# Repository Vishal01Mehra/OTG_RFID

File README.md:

# STM32G0 + MFRC522 RFID Reader

#### This repository provides code and hardware documentation for interfacing the **MFRC522 RFID reader** with an **STM32G0 series microcontroller** over SPI. The firmware initializes the MFRC522, detects RFID cards, and prints their UID over UART. It also includes support for an **addressable RGB LED** (e.g., WS2812B) and a **buzzer** for feedback.

##  Features
- Uses STM32Cube HAL for SPI, GPIO, and TIM
- Reads MIFARE cards (UID output)
- Controls an addressable RGB LED (PA3)
- Activates buzzer on card detection (PA2)
- Compatible with MFRC522 13.56 MHz modules
- Designed for STM32G0xx (e.g., STM32G071, STM32G031)
- Antenna is tuned for best theoretical range (10–15 cm)

>  **Note:** Higher read ranges (>15 cm) are only possible with UHF RFID chipsets (e.g., EPC Gen2, ISO18000-6C), which are significantly more expensive. This project limits itself to a 13.56 MHz MFRC522-based design due to a target **cost constraint of ₹500**, making UHF solutions out of scope.

---

##  Repository Structure
```
├── Core
│   ├── Inc
│   │   └── mfrc522.h           # MFRC522 header file
│   └── Src
│       └── mfrc522.c           # MFRC522 implementation
├── Drivers
│   └── STM32G0xx_HAL_Driver    # HAL drivers
├── README.md                   # This file
├── main.c                      # Main application logic
├── LICENSE                     # GNU GPL v3 license
└── .ioc                        # STM32CubeMX project file
```

---

##  Hardware Connections
### SPI Interface
| MFRC522 Pin | STM32G0 Pin | Description |
|-------------|-------------|-------------|
| SDA (SS)    | PA4         | SPI Chip Select |
| SCK         | PA5         | SPI Clock |
| MOSI        | PA7         | SPI MOSI |
| MISO        | PA6         | SPI MISO |
| RST         | PB0         | Reset Pin |
| 3.3V        | 3.3V        | Power |
| GND         | GND         | Ground |

### Other IOs
| Component         | STM32G0 Pin | Notes                       |
|-------------------|-------------|-----------------------------|
| Buzzer            | PA2         | On for tag detected         |
| RGB LED (WS2812B) | PA3         | 1-wire protocol             |

---

##  Example Output (USB)
```
MFRC522 Reader Initialized
Scan RFID...
UID: DE AD BE EF
```

---

##  Getting Started

### Prerequisites
- STM32CubeIDE or STM32CubeMX
- ST-LINK or compatible debugger
- MFRC522 RFID Module
- WS2812B LED
- Buzzer (active or transistor-driven passive)

### Build & Flash
1. Clone this repo: `https://github.com/Vishal01Mehra/OTG_RFID`
2. Open the `.ioc` file in STM32CubeIDE
3. Generate code and build
4. Flash to STM32G0 MCU

### Dependencies
- STM32 HAL Drivers (auto-imported with `.ioc`)

> 🔧 **Note:** Software is coming soon. Code files will be released as part of the first firmware version.

---

##  References
- [MFRC522 Datasheet](https://www.nxp.com/docs/en/data-sheet/MFRC522.pdf)
- [STM32G0 Reference Manual](https://www.st.com/resource/en/reference_manual/dm00371828.pdf)
- [WS2812B Timing](https://cdn-shop.adafruit.com/datasheets/WS2812B.pdf)

---

##  License
This project is licensed under the **GNU General Public License v3.0** - see the [LICENSE](LICENSE) file for details.

---

## Author
**Vishal Mehra** - Mehra Autonomous Systems Pvt. Ltd.

---

Feel free to contribute or raise issues via GitHub.

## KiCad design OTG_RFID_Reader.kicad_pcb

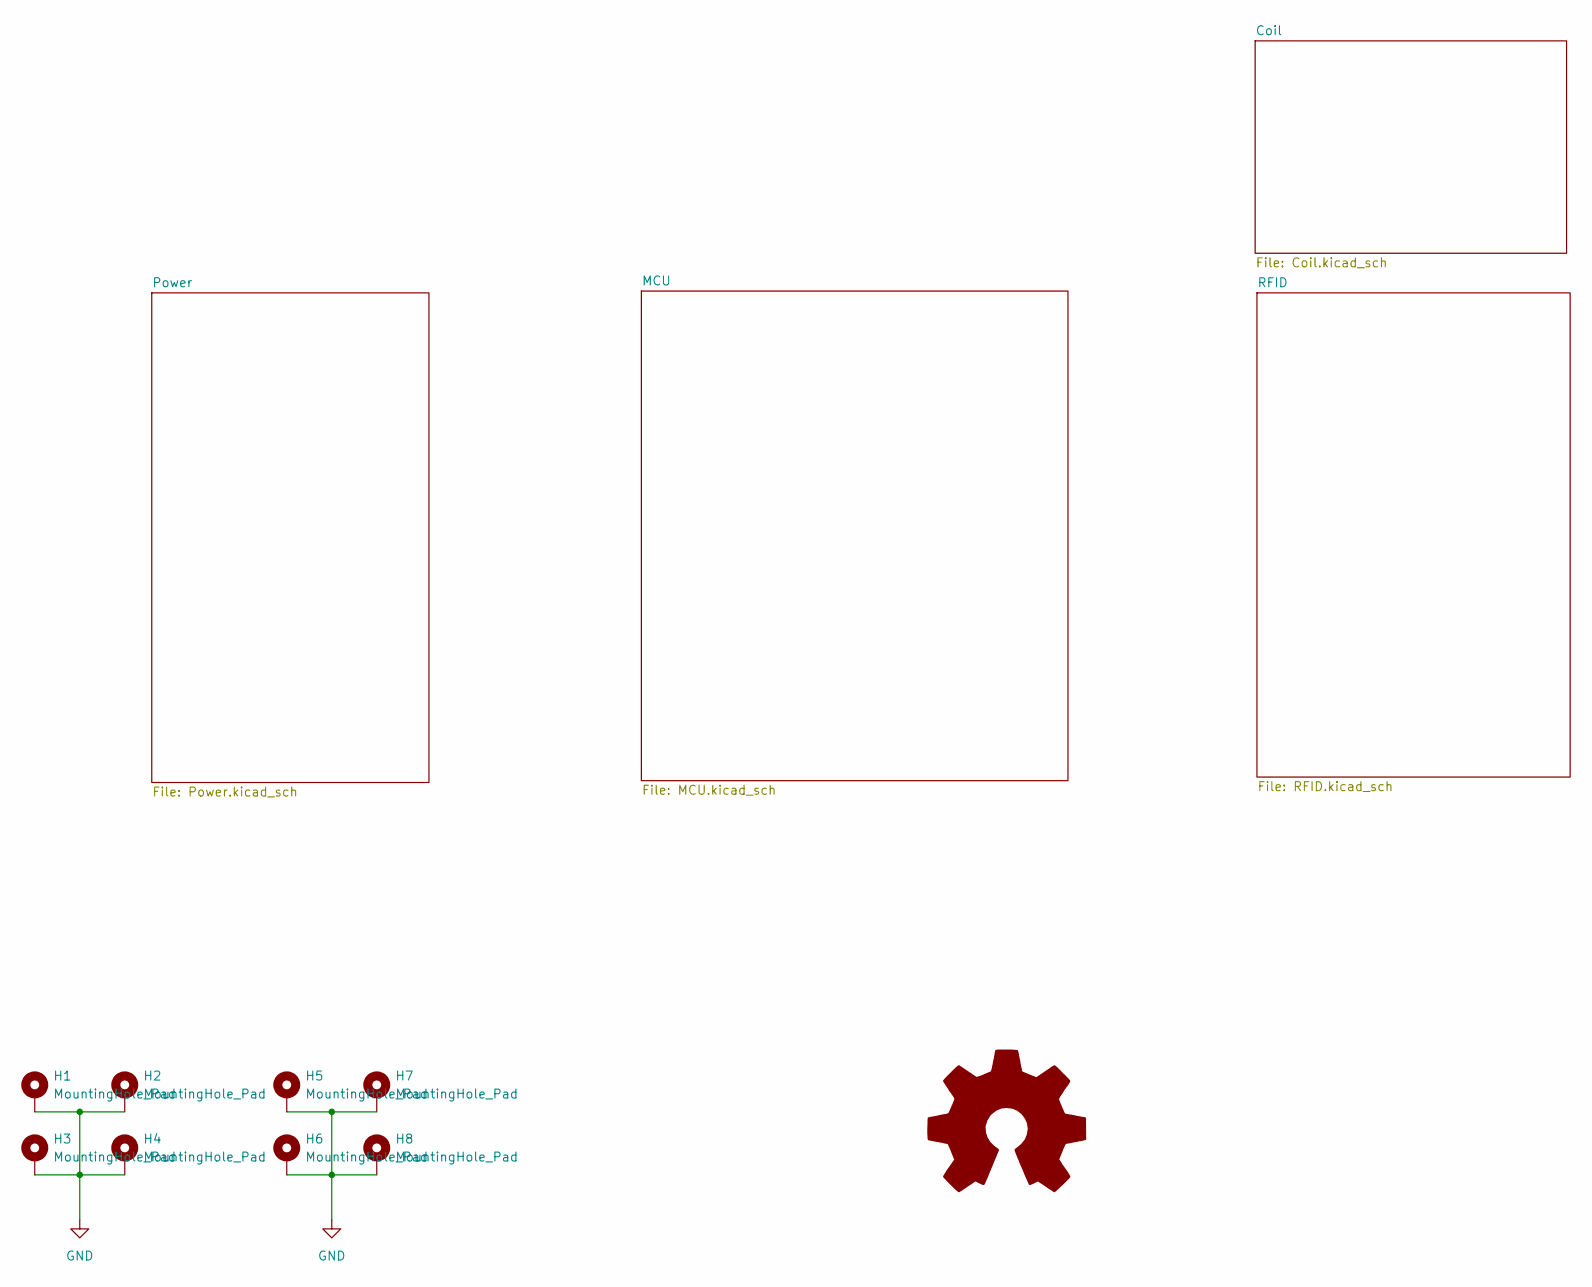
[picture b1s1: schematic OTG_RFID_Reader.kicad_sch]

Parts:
H1, H2, H3, H4, H5, H6, H7, H8: MountingHole_Pad; MountingHole_2.5mm_Pad

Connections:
GND: H1.1, H2.1, H3.1, H4.1, H5.1, H6.1, H7.1, H8.1; also elsewhere on the board

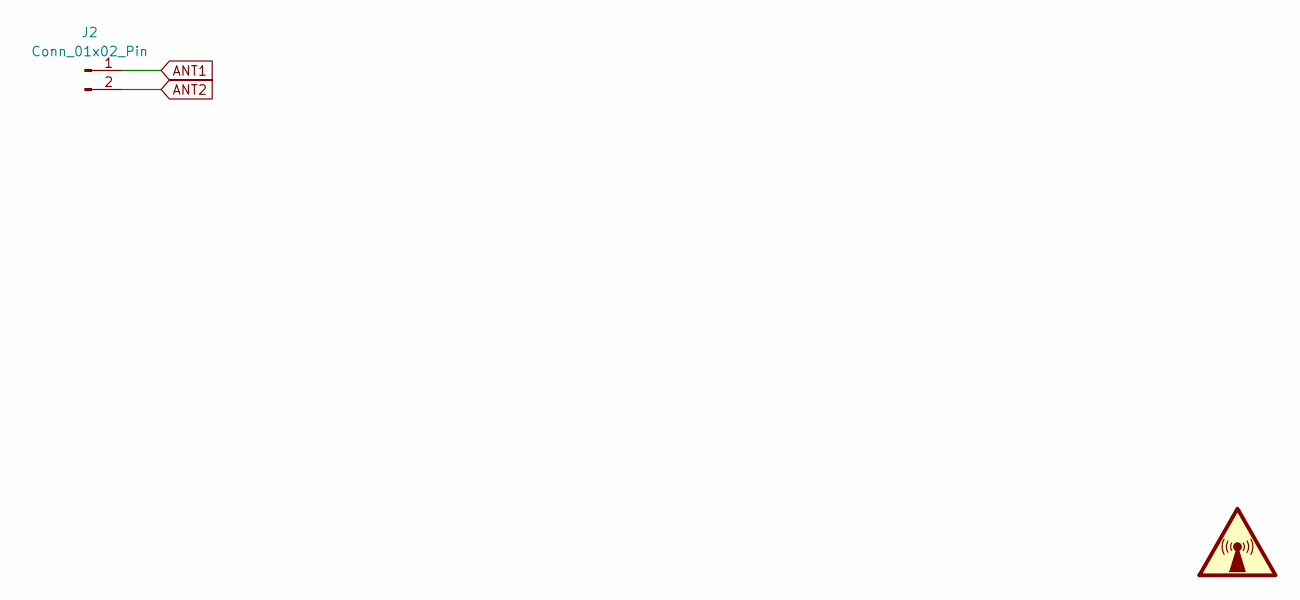
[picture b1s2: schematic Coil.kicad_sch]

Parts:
J2: Conn_01x02_Pin; PinSocket_1x02_P2.54mm_Vertical

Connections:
ANT1: J2.1; also elsewhere on the board
ANT2: J2.2; also elsewhere on the board

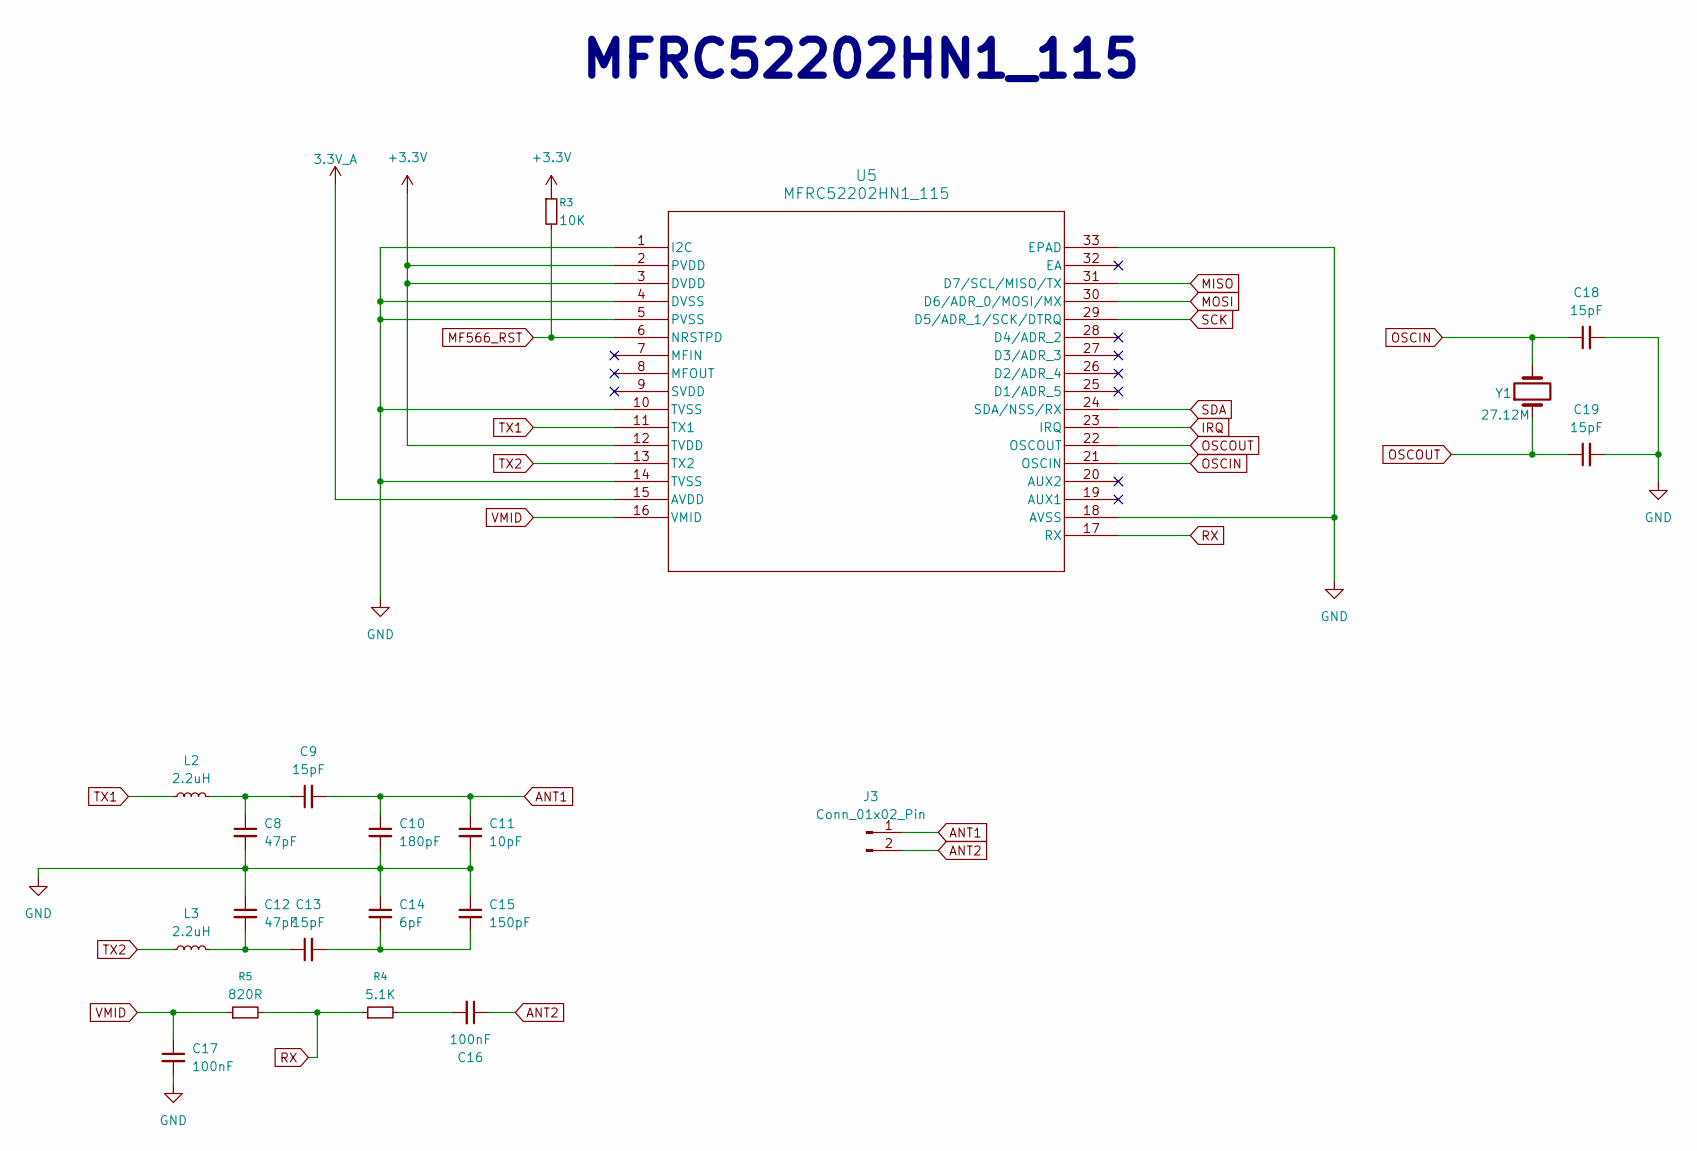
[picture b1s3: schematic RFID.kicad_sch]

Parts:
C8, C12: 47pF; C_0603_1608Metric
C9, C13, C18, C19: 15pF; C_0603_1608Metric
C10: 180pF; C_0603_1608Metric
C11: 10pF; C_0603_1608Metric
C14: 6pF; C_0603_1608Metric
C15: 150pF; C_0603_1608Metric
C16, C17: 100nF; C_0603_1608Metric
J3: Conn_01x02_Pin; PinSocket_1x02_P2.54mm_Vertical
L2, L3: 2.2uH; L_0603_1608Metric
R3: 10K; R_0603_1608Metric
R4: 5.1K; R_0603_1608Metric
R5: 820R; R_0603_1608Metric
U5: MFRC52202HN1_115; HVQFN32_SOT617-1_NXP
Y1: 27.12M; Crystal_SMD_TXC_7A-2Pin_5x3.2mm

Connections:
3.3V_A: U5.15 (AVDD); also elsewhere on the board
+3.3V: R3.1, U5.2 (PVDD), U5.3 (DVDD), U5.12 (TVDD); also elsewhere on the board
ANT1: C9.2, C10.1, C11.1, J3.1; also elsewhere on the board
ANT2: C16.1, J3.2; also elsewhere on the board
GND: C8.2, C10.2, C11.2, C12.1, C14.1, C15.1, C17.2, C18.2, C19.2, U5.1 (I2C), U5.4 (DVSS), U5.5 (PVSS), U5.10 (TVSS), U5.14 (TVSS), U5.18 (AVSS), U5.33 (EPAD); also elsewhere on the board
IRQ: U5.23 (IRQ)
MF566_RST: R3.2, U5.6 (NRSTPD)
MISO: U5.31 (D7/SCL/MISO/TX); also elsewhere on the board
MOSI: U5.30 (D6/ADR_0/MOSI/MX); also elsewhere on the board
unnamed: C8.1, C9.1, L2.2
unnamed: C12.2, C13.1, L3.2
unnamed: C13.2, C14.2, C15.2
unnamed: C16.2, R4.2
OSCIN: C18.1, U5.21 (OSCIN), Y1.2
OSCOUT: C19.1, U5.22 (OSCOUT), Y1.1
RX: R4.1, R5.2, U5.17 (RX)
SCK: U5.29 (D5/ADR_1/SCK/DTRQ); also elsewhere on the board
SDA: U5.24 (SDA/NSS/RX); also elsewhere on the board
TX1: L2.1, U5.11 (TX1)
TX2: L3.1, U5.13 (TX2)
VMID: C17.1, R5.1, U5.16 (VMID)

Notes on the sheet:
MFRC52202HN1_115

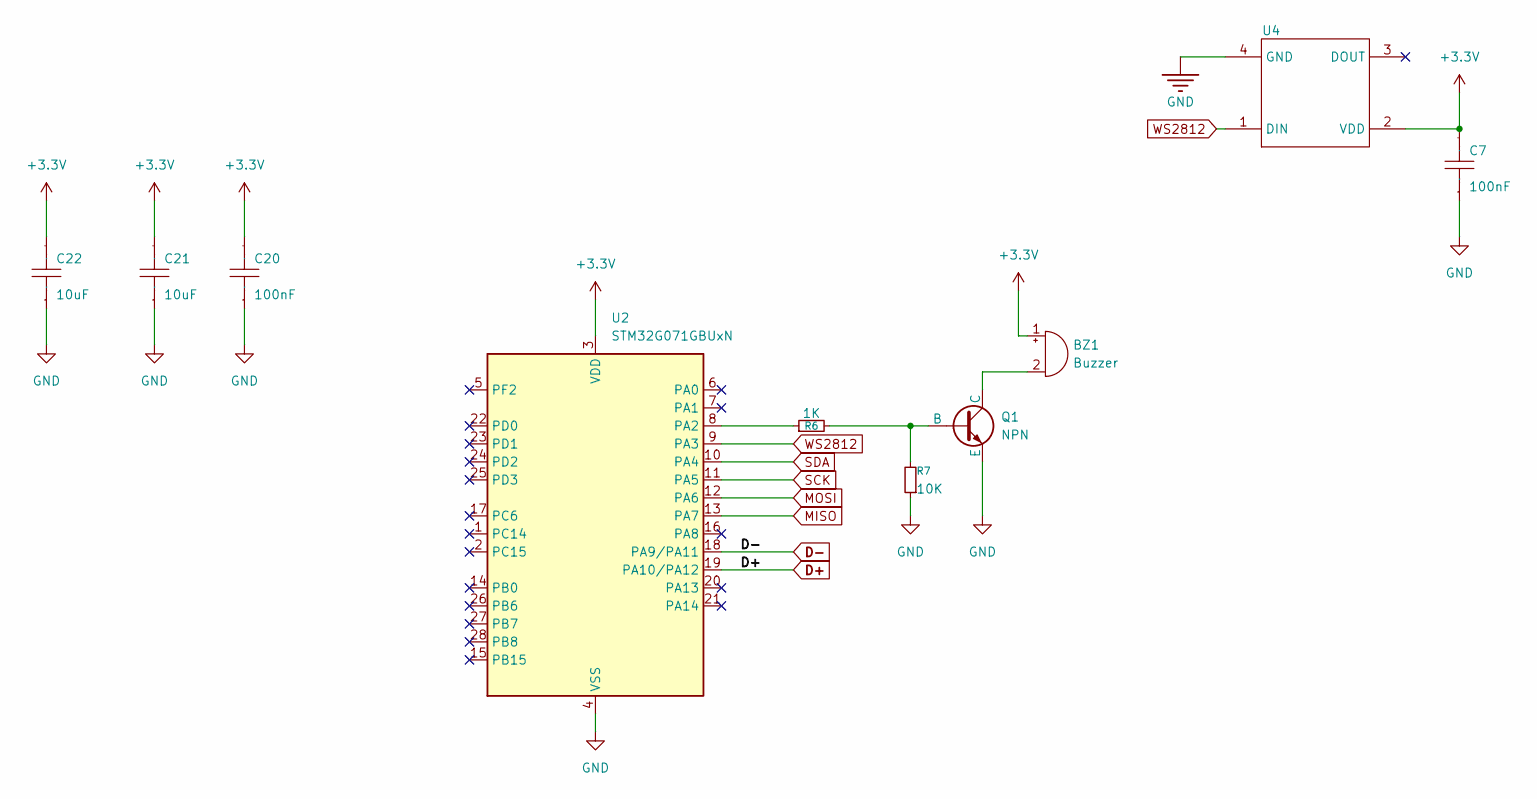
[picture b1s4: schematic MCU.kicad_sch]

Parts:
BZ1: Buzzer; MagneticBuzzer_CUI_CMT-8504-100-SMT
C7, C20: 100nF; C_0603_1608Metric
C21, C22: 10uF; C_0603_1608Metric
Q1: NPN; SOT-323_SC-70
R6: 1K; R_0603_1608Metric
R7: 10K; R_0603_1608Metric
U2: STM32G071GBUxN; QFN-28_4x4mm_P0.5mm
U4: LED_WS2812B-2020_PLCC4_2.0x2.0mm

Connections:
+3.3V: BZ1.1 (+), C7.2, C20.2, C21.2, C22.2, U2.3 (VDD), U4.2 (VDD); also elsewhere on the board
D+: U2.19 (PA10/PA12); also elsewhere on the board
D-: U2.18 (PA9/PA11); also elsewhere on the board
GND: C7.1, C20.1, C21.1, C22.1, Q1.3 (E), R7.1, U2.4 (VSS), U4.4 (GND); also elsewhere on the board
MISO: U2.13 (PA7); also elsewhere on the board
MOSI: U2.12 (PA6); also elsewhere on the board
unnamed: BZ1.2 (-), Q1.1 (C)
unnamed: Q1.2 (B), R6.2, R7.2
unnamed: R6.1, U2.8 (PA2)
SCK: U2.11 (PA5); also elsewhere on the board
SDA: U2.10 (PA4); also elsewhere on the board
WS2812: U2.9 (PA3), U4.1 (DIN)

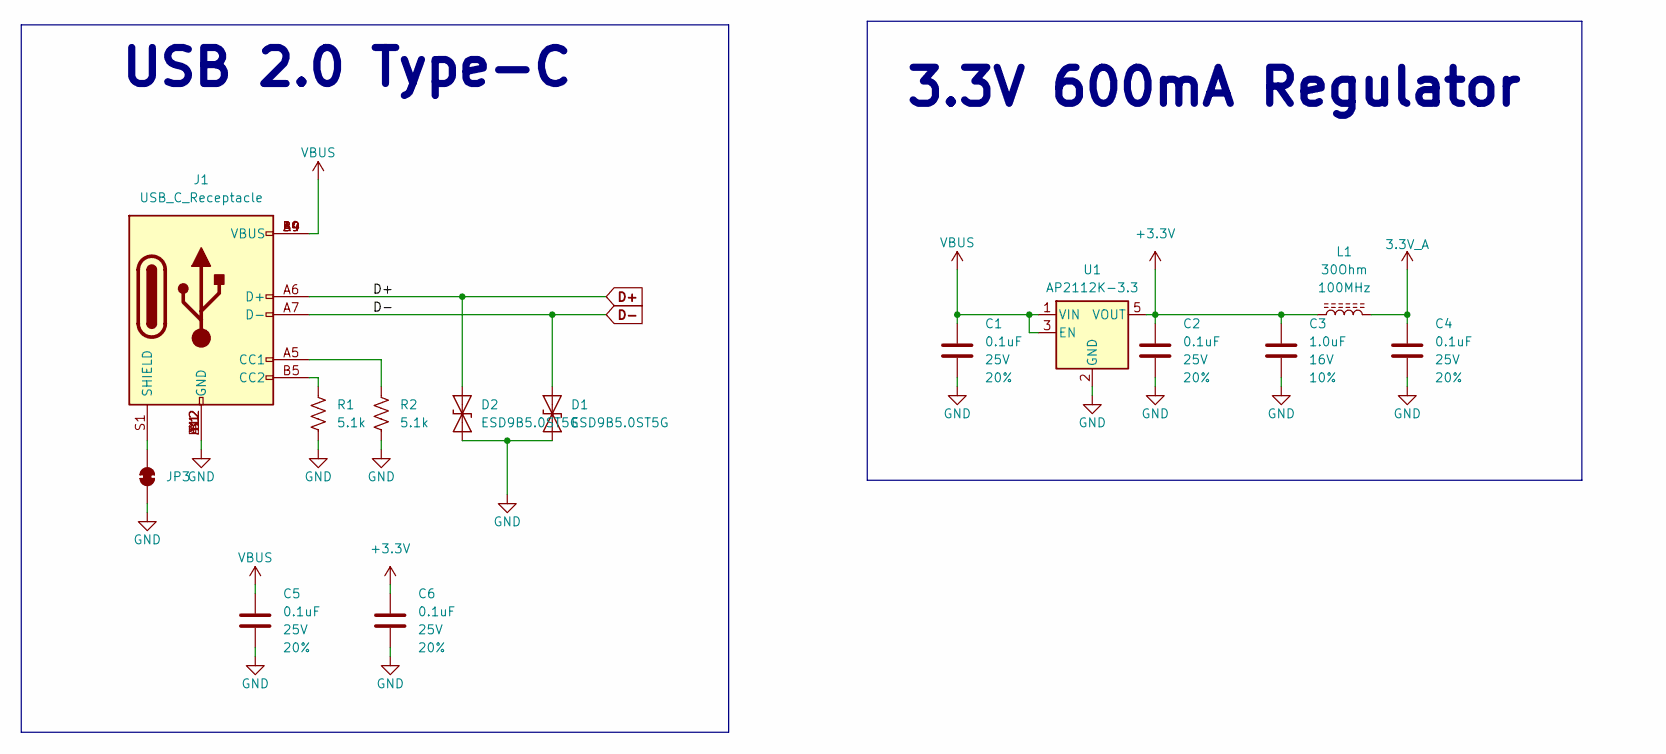
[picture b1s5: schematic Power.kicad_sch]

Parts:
C1, C2, C4, C5, C6: 0.1uF; C_0603_1608Metric; Voltage 25V; Tolerance 20%
C3: 1.0uF; C_0603_1608Metric; Voltage 16V; Tolerance 10%
D1, D2: ESD9B5.0ST5G; D_SOD-923
J1: USB_C_Receptacle; USB_C_Receptacle_GCT_USB4105-xx-A_16P_TopMnt_Horizontal
JP3: SolderJumper-2_P1.3mm_Bridged2Bar_RoundedPad1.0x1.5mm
L1: 30Ohm; L_0603_1608Metric
R1, R2: 5.1k; R_0603_1608Metric
U1: AP2112K-3.3; SOT-23-5_HandSoldering

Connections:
3.3V_A: C4.1, L1.2; also elsewhere on the board
+3.3V: C2.1, C3.1, C6.1, L1.1, U1.5 (VOUT); also elsewhere on the board
D+: D2.1 (A1), J1.A6 (D+), J1.B6 (D+); also elsewhere on the board
D-: D1.1 (A1), J1.A7 (D-), J1.B7 (D-); also elsewhere on the board
GND: C1.2, C2.2, C3.2, C4.2, C5.2, C6.2, D1.2 (A2), D2.2 (A2), J1.A1 (GND), J1.A12 (GND), J1.B1 (GND), J1.B12 (GND), JP3.1 (A), R1.2, R2.2, U1.2 (GND); also elsewhere on the board
unnamed: J1.A5 (CC1), R2.1
unnamed: J1.B5 (CC2), R1.1
unnamed: J1.S1 (SHIELD), JP3.2 (B)
VBUS: C1.1, C5.1, J1.A4 (VBUS), J1.A9 (VBUS), J1.B4 (VBUS), J1.B9 (VBUS), U1.1 (VIN), U1.3 (EN)

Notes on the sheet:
3.3V 600mA Regulator
USB 2.0 Type-C

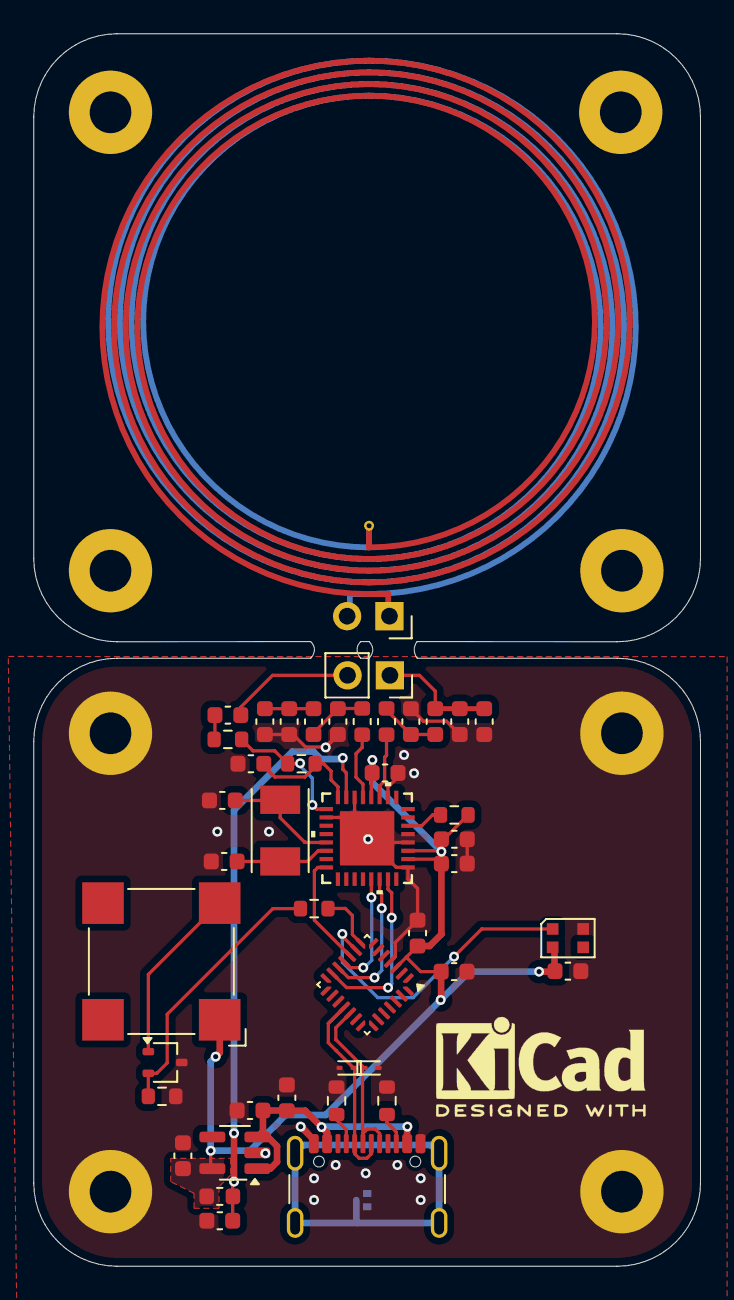
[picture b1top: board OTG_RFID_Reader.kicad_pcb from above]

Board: 2 copper layers, 40.0 x 73.9 mm, 53 parts (1 on the bottom side), 30 nets.

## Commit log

2025-06-09 Added Project Files
